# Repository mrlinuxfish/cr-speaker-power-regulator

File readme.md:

# Power Regulator for CR3 / CR4

This pcb is designed to replace voltage regulator on Mackie CR3 / CR4 as described in [this writeup](https://www.mikrocontroller.net/articles/Mackie_Creative_Reference_CR3_CR4_Reparatur_Repair).

## BOM
| QTY   | Part                          | Recommended part number   |
|-------|-------------------------------|---------------------------|
| 4     | .1uf Capacitor                | K104K20X7RK53H5G          |
| 4     | Diode                         | 1n4148                    |
| 1     | Voltage Regulator (positive)  | L7812ABV                  |
| 1     | Voltage Regulator (negative)  | L7912ACV                  |

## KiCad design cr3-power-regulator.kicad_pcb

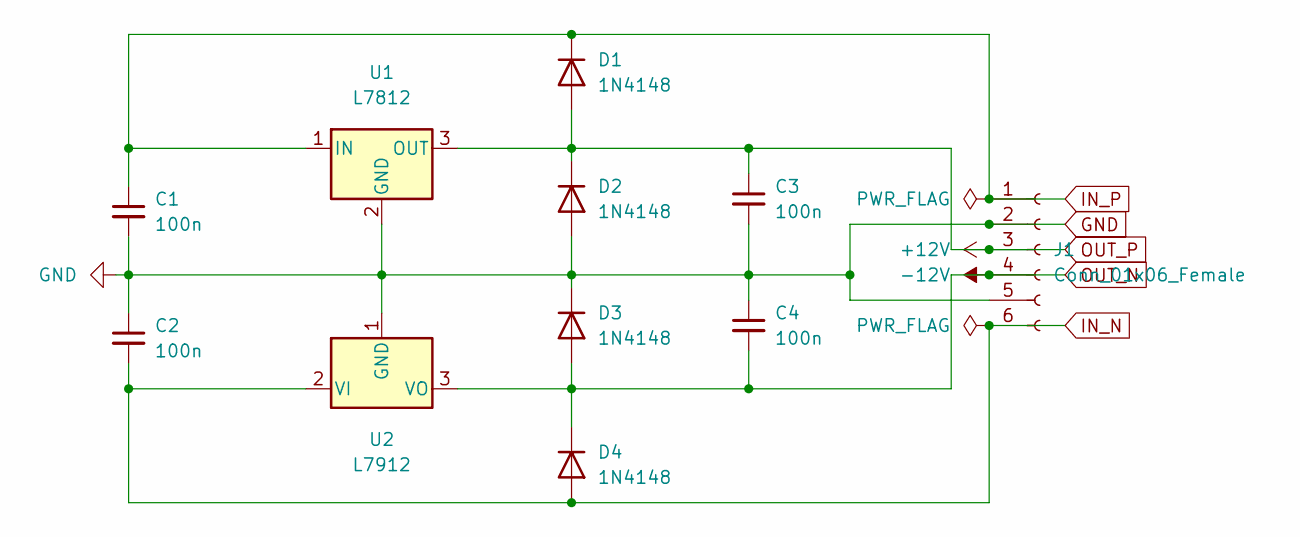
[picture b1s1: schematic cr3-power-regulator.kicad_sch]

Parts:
C1, C2, C3, C4: 100n; CP_Radial_Tantal_D5.0mm_P2.50mm
D1, D2, D3, D4: 1N4148; D_DO-35_SOD27_P7.62mm_Horizontal
J1: Conn_01x06_Female; PinHeader_1x06_P2.54mm_Vertical
U1: L7812; TO-220-3_Vertical
U2: L7912; TO-220-3_Vertical

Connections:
GND: C1.2, C2.1, C3.2, C4.1, D2.2 (A), D3.1 (K), J1.2, J1.5, U1.2 (GND), U2.1 (GND)
IN_N: C2.2, D4.2 (A), J1.6, U2.2 (VI)
IN_P: C1.1, D1.1 (K), J1.1, U1.1 (IN)
OUT_N: C4.2, D3.2 (A), D4.1 (K), J1.4, U2.3 (VO)
OUT_P: C3.1, D1.2 (A), D2.1 (K), J1.3, U1.3 (OUT)

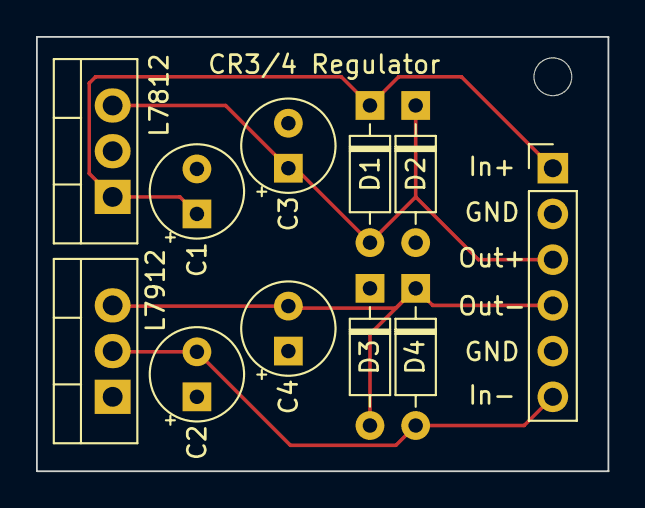
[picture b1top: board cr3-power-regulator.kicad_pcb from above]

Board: 2 copper layers, 31.8 x 24.1 mm, 11 parts (0 on the bottom side), 5 nets.

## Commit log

2022-01-12 Create LICENSE
2022-01-12 Fix formatting
2022-01-12 Fix table rendering
2022-01-12 Update pcb
2022-01-21 Update footprints
    - 1mm headder was accidentally used instead of 2.54mm (.1")
    - Regulators have correct footprint
    - Capacitors updated to use polarized footprints (in case it matters)
2022-01-21 Update silks
2022-01-21 Rotate caps
    All capacitors are in the same orientation which should aid in assembly
